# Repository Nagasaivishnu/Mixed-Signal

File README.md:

# Mixed-Signal
The following Eagle Project is just made by me to gain the experience in designing  Digital and Analog circuits.
It is 4 Layer board and JLCPCB Layer stack up has been used

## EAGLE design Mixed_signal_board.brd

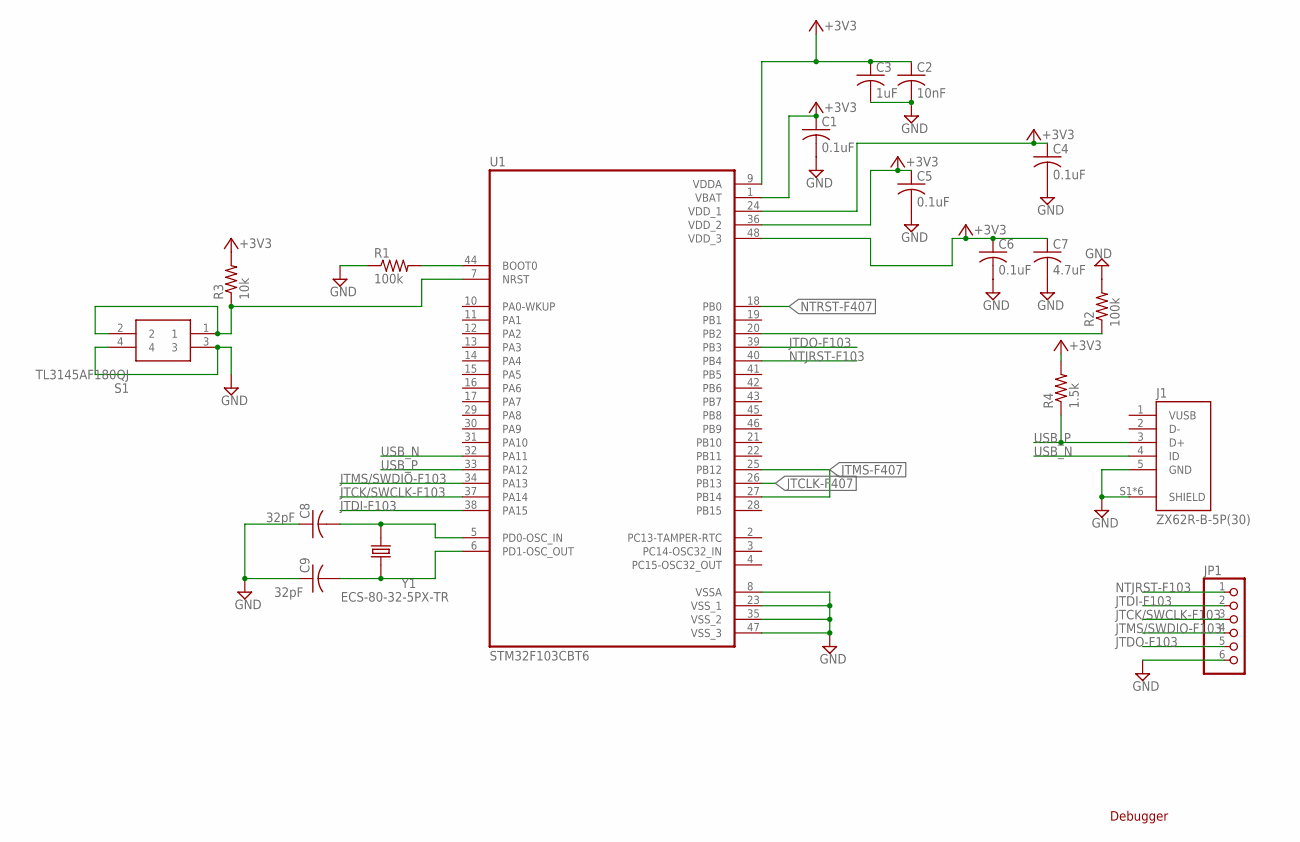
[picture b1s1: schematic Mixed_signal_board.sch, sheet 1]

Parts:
C1, C4, C5, C6: 0.1uF; C0805
C2: 10nF; C0805
C3: 1uF; C0805
C7: 4.7uF; C0805
C8, C9: 32pF; C0805
J1: ZX62R-B-5P(30); HRS_ZX62R-B-5P(30)
JP1: PINHD-1X6; 1X06
R1, R2: 100k; R0805
R3: 10k; R0805
R4: 1.5k; R0805
S1: TL3145AF180QJ
U1: STM32F103CBT6; QFP50P900X900X160-48N
Y1: ECS-80-32-5PX-TR; XTAL_ECS-80-32-5PX-TR

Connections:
+3V3: C1.1, C2.1, C3.1, C4.1, C5.1, C6.1, C7.1, R3.2, R4.2, U1.1 (VBAT), U1.9 (VDDA), U1.24 (VDD_1), U1.36 (VDD_2), U1.48 (VDD_3); also elsewhere on the board
GND: C1.2, C2.2, C3.2, C4.2, C5.2, C6.2, C7.2, C8.1, C9.1, J1.5 (GND), J1.S1 (SHIELD), J1.S2 (SHIELD), J1.S3 (SHIELD), J1.S4 (SHIELD), J1.S5 (SHIELD), J1.S6 (SHIELD), JP1.6, R1.1, R2.2, S1.3, S1.4, U1.8 (VSSA), U1.23 (VSS_1), U1.35 (VSS_2), U1.47 (VSS_3); also elsewhere on the board
JTCK/SWCLK-F103: JP1.3, U1.37 (PA14)
JTCLK-F407: U1.26 (PB13); also elsewhere on the board
JTDI-F103: JP1.2, U1.38 (PA15)
JTDO-F103: JP1.5, U1.39 (PB3)
JTMS-F407: U1.25 (PB12), U1.27 (PB14); also elsewhere on the board
JTMS/SWDIO-F103: JP1.4, U1.34 (PA13)
unnamed: R1.2, U1.44 (BOOT0)
unnamed: R2.1, U1.20 (PB2)
unnamed: C8.2, U1.5 (PD0-OSC_IN), Y1.2
unnamed: C9.2, U1.6 (PD1-OSC_OUT), Y1.1
unnamed: R3.1, S1.1, S1.2, U1.7 (NRST)
NTJRST-F103: JP1.1, U1.40 (PB4)
NTRST-F407: U1.18 (PB0)
USB_N: J1.4 (ID), U1.32 (PA11)
USB_P: J1.3 (D+), R4.1, U1.33 (PA12)

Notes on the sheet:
Debugger

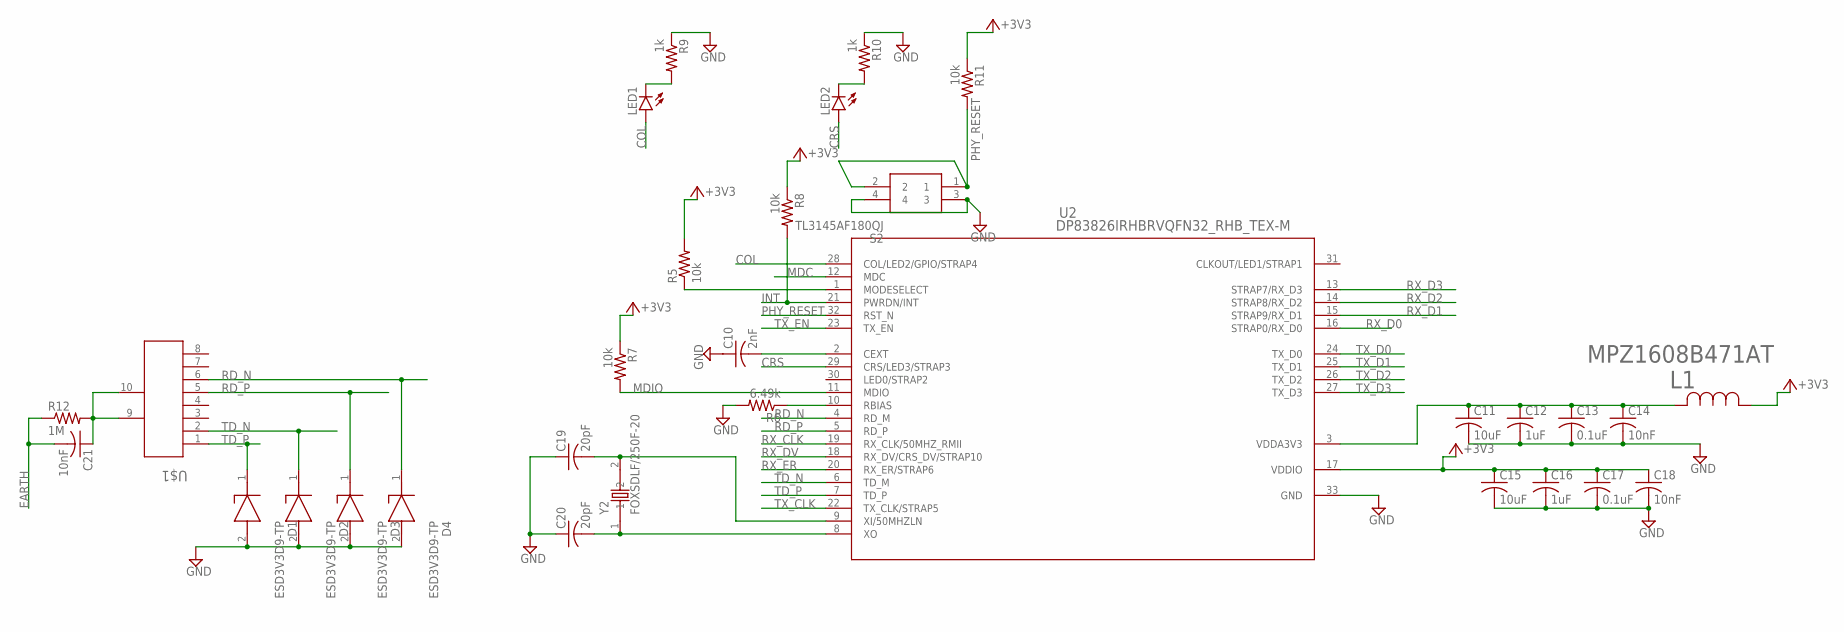
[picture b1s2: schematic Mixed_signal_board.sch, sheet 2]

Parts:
C10: 2nF; C0805
C11, C15: 10uF; C0805
C12, C16: 1uF; C0805
C13, C17: 0.1uF; C0805
C14, C18, C21: 10nF; C0805
C19, C20: 20pF; C0805
D1, D2, D3, D4: ESD3V3D9-TP; SODFL1006X43N
L1: MPZ1608B471AT; IND_MPZ1608_TDK
LED1, LED2: LEDCHIPLED_0805; CHIPLED_0805
R5, R7, R8, R11: 10k; R0805
R6: 6.49k; R0805
R9, R10: 1k; R0805
R12: 1M; R0805
S2: TL3145AF180QJ
U2: DP83826IRHBRVQFN32_RHB_TEX-M; VQFN32_RHB_TEX-M
U$1: RJ-45; CONN_RJSBE5080_16P13X12P57_AMP
Y2: FOXSDLF/250F-20; XTAL1170X500X450

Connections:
+3V3: C15.1, C16.1, C17.1, C18.1, L1.1, R5.2, R7.1, R8.1, R11.1, U2.17 (VDDIO); also elsewhere on the board
COL: LED1.A, U2.28 (COL/LED2/GPIO/STRAP4); also elsewhere on the board
CRS: LED2.A, U2.29 (CRS/LED3/STRAP3); also elsewhere on the board
EARTH: C21.2, R12.1; also elsewhere on the board
GND: C10.1, C11.2, C12.2, C13.2, C14.2, C15.2, C16.2, C17.2, C18.2, C19.1, C20.1, D1.2 (A), D2.2 (A), D3.2 (A), D4.2 (A), R6.2, R9.1, R10.1, S2.3, S2.4, U2.33 (GND); also elsewhere on the board
INT: R8.2, U2.21 (PWRDN/INT)
MDC: U2.12 (MDC); also elsewhere on the board
MDIO: R7.2, U2.11 (MDIO); also elsewhere on the board
unnamed: R5.1, U2.1 (MODESELECT)
unnamed: C10.2, U2.2 (CEXT)
unnamed: C11.1, C12.1, C13.1, C14.1, L1.2, U2.3 (VDDA3V3)
unnamed: C19.2, U2.9 (XI/50MHZLN), Y2.2
unnamed: C20.2, U2.8 (XO), Y2.1
unnamed: R6.1, U2.10 (RBIAS)
unnamed: C21.1, R12.2, U$1.9 (EARTH), U$1.10 (EARTH2)
unnamed: LED1.C, R9.2
unnamed: LED2.C, R10.2
PHY_RESET: R11.2, S2.1, S2.2, U2.32 (RST_N); also elsewhere on the board
RD_N: D4.1 (K), U2.4 (RD_M), U$1.6 (D3-)
RD_P: D3.1 (K), U2.5 (RD_P), U$1.5 (D3+)
RX_CLK: U2.19 (RX_CLK/50MHZ_RMII); also elsewhere on the board
RX_D0: U2.16 (STRAP0/RX_D0); also elsewhere on the board
RX_D1: U2.15 (STRAP9/RX_D1); also elsewhere on the board
RX_D2: U2.14 (STRAP8/RX_D2); also elsewhere on the board
RX_D3: U2.13 (STRAP7/RX_D3); also elsewhere on the board
RX_DV: U2.18 (RX_DV/CRS_DV/STRAP10); also elsewhere on the board
RX_ER: U2.20 (RX_ER/STRAP6)
TD_N: D2.1 (K), U2.6 (TD_M), U$1.2 (D1-)
TD_P: D1.1 (K), U2.7 (TD_P), U$1.1 (D1+)
TX_CLK: U2.22 (TX_CLK/STRAP5); also elsewhere on the board
TX_D0: U2.24 (TX_D0); also elsewhere on the board
TX_D1: U2.25 (TX_D1); also elsewhere on the board
TX_D2: U2.26 (TX_D2); also elsewhere on the board
TX_D3: U2.27 (TX_D3); also elsewhere on the board
TX_EN: U2.23 (TX_EN); also elsewhere on the board

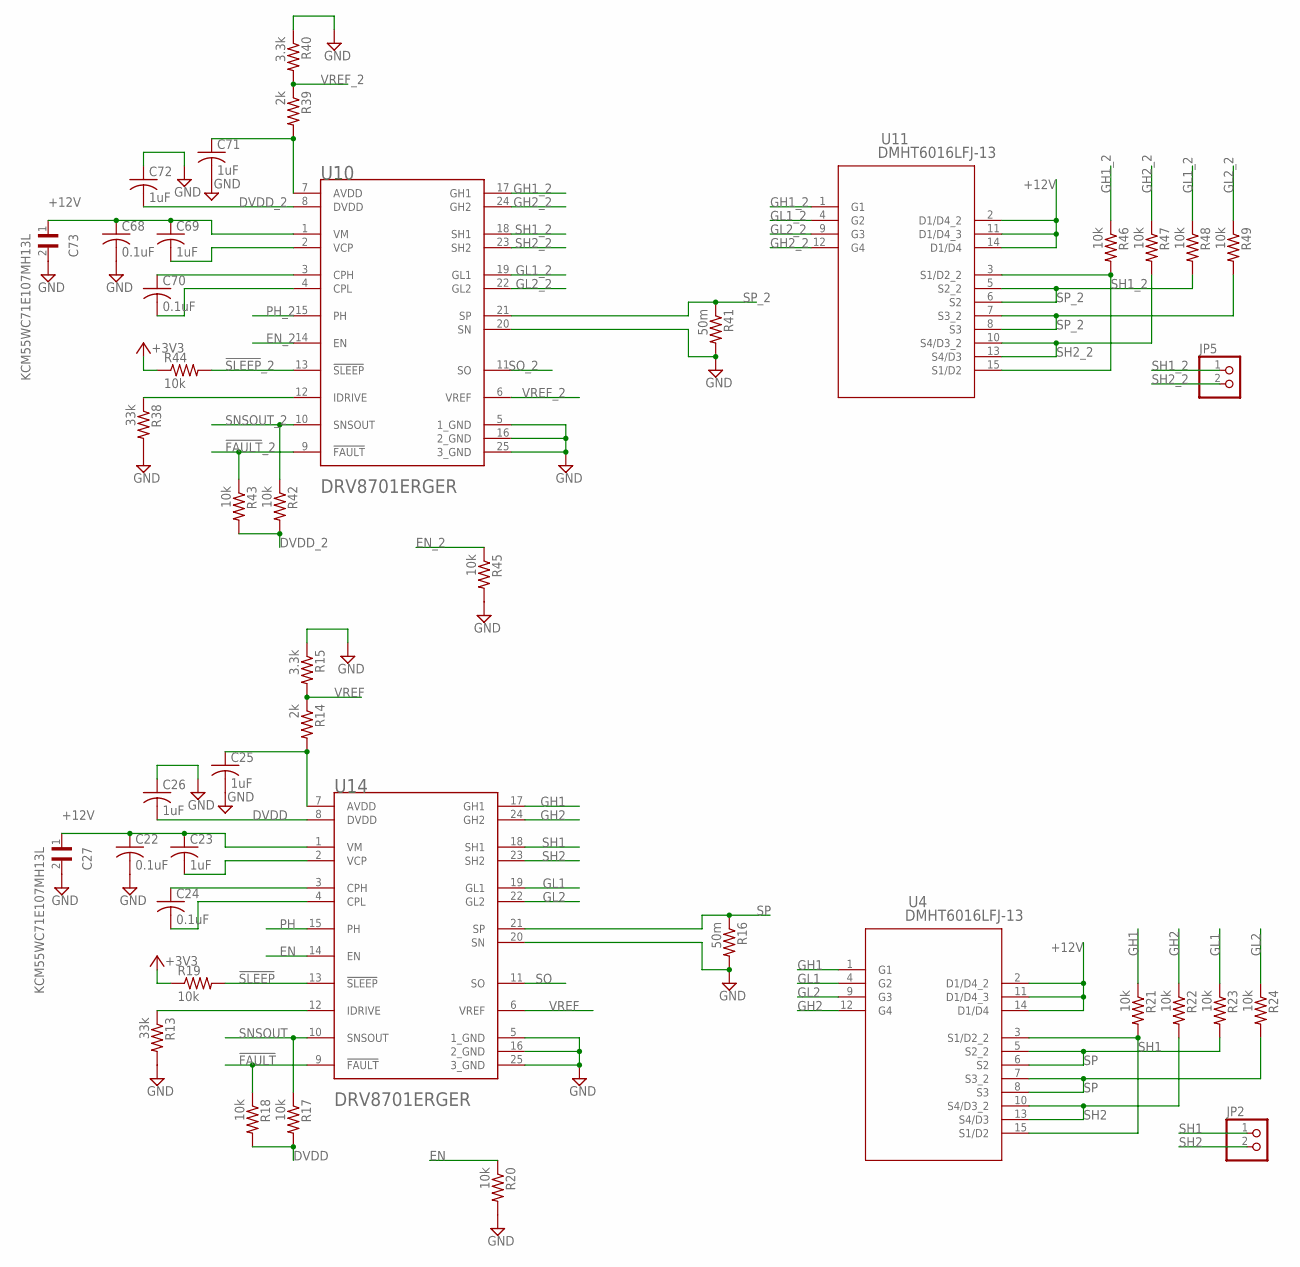
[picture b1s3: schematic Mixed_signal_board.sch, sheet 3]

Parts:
C22, C24, C68, C70: 0.1uF; C0805
C23, C25, C26, C69, C71, C72: 1uF; C0805
C27, C73: KCM55WC71E107MH13L; CAPC6153X670N
JP2, JP5: PINHD-1X2; 1X02
R13, R38: 33k; R0805
R14, R39: 2k; R0805
R15, R40: 3.3k; R0805
R16, R41: 50m; R0805
R17, R18, R19, R20, R21, R22, R23, R24, R42, R43, R44, R45, R46, R47, R48, R49: 10k; R0805
U4, U11: DMHT6016LFJ-13; QFN_LFJ-13_DIO
U10, U14: TEXAS_INSTRUMENTS_DRV8701ERGERTEXAS_INSTRUMENTS_D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; TEXAS_INSTRUMENTS_DRV8701ERGER_0

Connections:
!FAULT!: R18.1, U14.9 (!FAULT!); also elsewhere on the board
!FAULT!_2: R43.1, U10.9 (!FAULT!); also elsewhere on the board
!SLEEP!: R19.2, U14.13 (!SLEEP!)
!SLEEP!_2: R44.2, U10.13 (!SLEEP!)
+3V3: R19.1, R44.1; also elsewhere on the board
+12V: C22.1, C23.1, C27.1, C68.1, C69.1, C73.1, U4.2 (D1/D4_2), U4.11 (D1/D4_3), U4.14 (D1/D4), U10.1 (VM), U11.2 (D1/D4_2), U11.11 (D1/D4_3), U11.14 (D1/D4), U14.1 (VM); also elsewhere on the board
DVDD: C26.2, R17.2, R18.2, U14.8 (DVDD)
DVDD_2: C72.2, R42.2, R43.2, U10.8 (DVDD)
EN: R20.1, U14.14 (EN); also elsewhere on the board
EN_2: R45.1, U10.14 (EN); also elsewhere on the board
GH1: R21.1, U4.1 (G1), U14.17 (GH1)
GH1_2: R46.1, U10.17 (GH1), U11.1 (G1)
GH2: R22.1, U4.12 (G4), U14.24 (GH2)
GH2_2: R47.1, U10.24 (GH2), U11.12 (G4)
GL1: R23.1, U4.4 (G2), U14.19 (GL1)
GL1_2: R48.1, U10.19 (GL1), U11.4 (G2)
GL2: R24.1, U4.9 (G3), U14.22 (GL2)
GL2_2: R49.1, U10.22 (GL2), U11.9 (G3)
GND: C22.2, C25.2, C26.1, C27.2, C68.2, C71.2, C72.1, C73.2, R13.2, R15.1, R16.2, R20.2, R38.2, R40.1, R41.2, R45.2, U10.5 (1_GND), U10.16 (2_GND), U10.20 (SN), U10.25 (3_GND), U14.5 (1_GND), U14.16 (2_GND), U14.20 (SN), U14.25 (3_GND); also elsewhere on the board
unnamed: C23.2, U14.2 (VCP)
unnamed: C24.1, U14.3 (CPH)
unnamed: C24.2, U14.4 (CPL)
unnamed: R13.1, U14.12 (IDRIVE)
unnamed: C25.1, R14.2, U14.7 (AVDD)
unnamed: C69.2, U10.2 (VCP)
unnamed: C70.1, U10.3 (CPH)
unnamed: C70.2, U10.4 (CPL)
unnamed: R38.1, U10.12 (IDRIVE)
unnamed: C71.1, R39.2, U10.7 (AVDD)
PH: U14.15 (PH); also elsewhere on the board
PH_2: U10.15 (PH); also elsewhere on the board
SH1: JP2.1, R21.2, U4.3 (S1/D2_2), U4.15 (S1/D2), U14.18 (SH1)
SH1_2: JP5.1, R46.2, U10.18 (SH1), U11.3 (S1/D2_2), U11.15 (S1/D2)
SH2: JP2.2, R22.2, U4.10 (S4/D3_2), U4.13 (S4/D3), U14.23 (SH2)
SH2_2: JP5.2, R47.2, U10.23 (SH2), U11.10 (S4/D3_2), U11.13 (S4/D3)
SNSOUT: R17.1, U14.10 (SNSOUT); also elsewhere on the board
SNSOUT_2: R42.1, U10.10 (SNSOUT); also elsewhere on the board
SO: U14.11 (SO); also elsewhere on the board
SO_2: U10.11 (SO); also elsewhere on the board
SP: R16.1, R23.2, R24.2, U4.5 (S2_2), U4.6 (S2), U4.7 (S3_2), U4.8 (S3), U14.21 (SP)
SP_2: R41.1, R48.2, R49.2, U10.21 (SP), U11.5 (S2_2), U11.6 (S2), U11.7 (S3_2), U11.8 (S3)
VREF: R14.1, R15.2, U14.6 (VREF)
VREF_2: R39.1, R40.2, U10.6 (VREF)

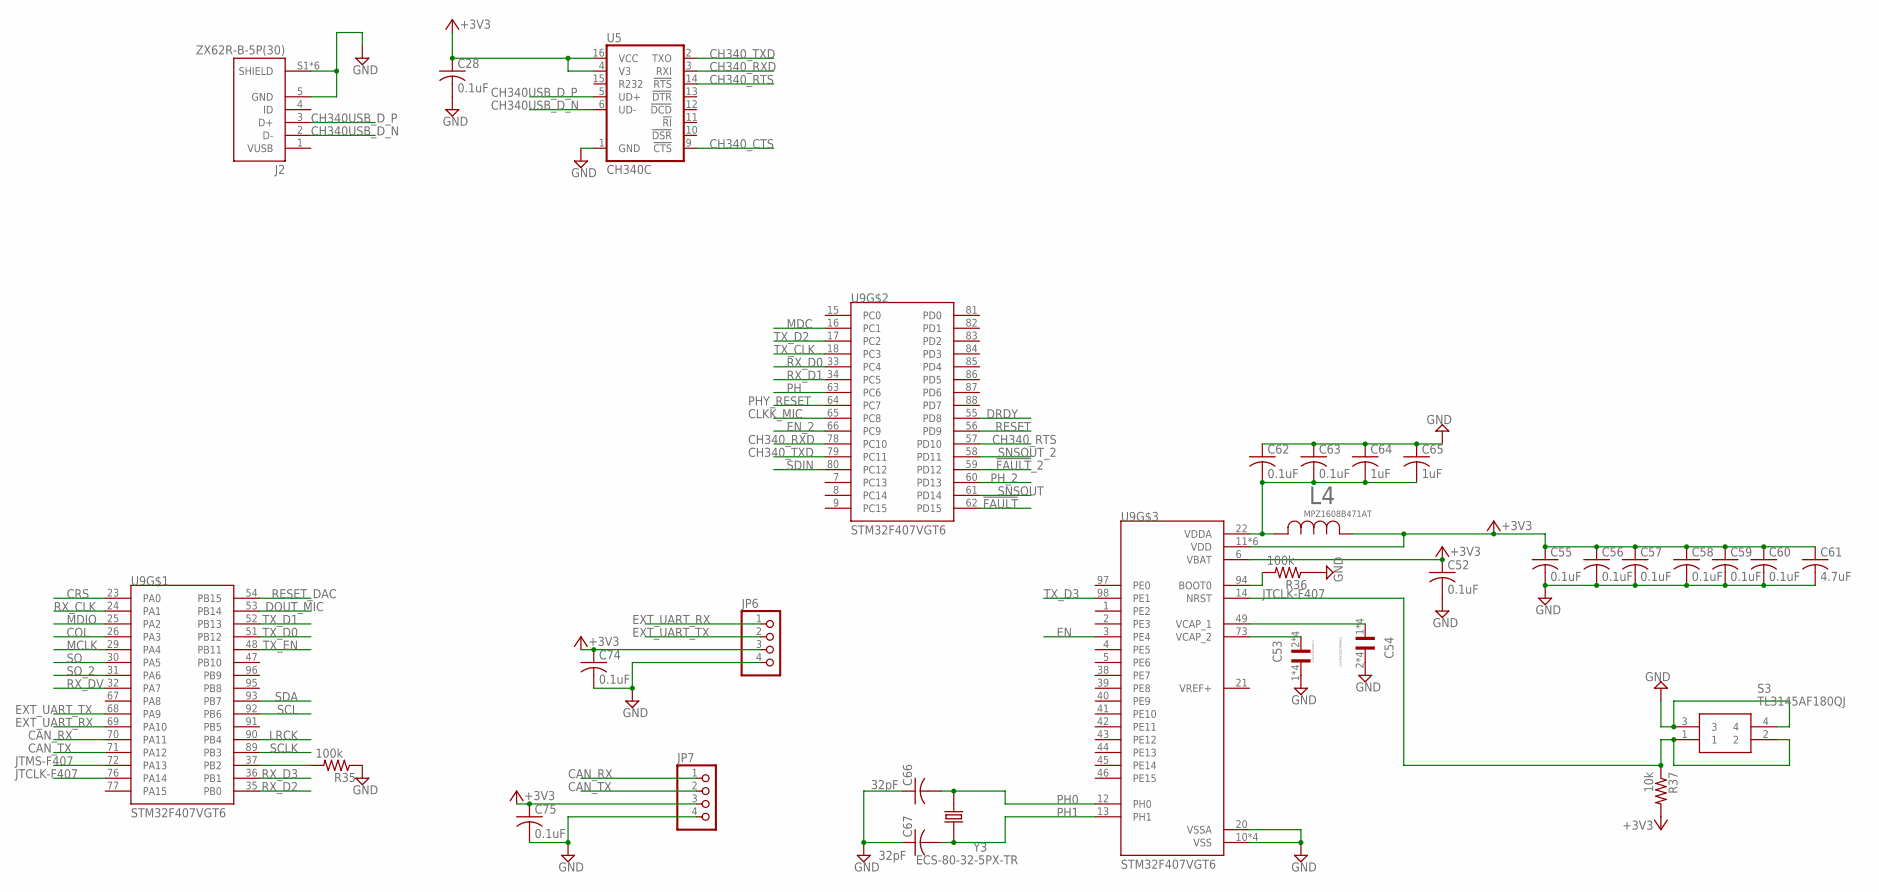
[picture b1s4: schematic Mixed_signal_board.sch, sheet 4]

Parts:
C28, C52, C55, C56, C57, C58, C59, C60, C62, C63, C74, C75: 0.1uF; C0805
C53, C54: LLA219C70G225MA01L; CAP_LLA219C70G225MA01L
C61: 4.7uF; C0805
C64, C65: 1uF; C0805
C66, C67: 32pF; C0805
J2: ZX62R-B-5P(30); HRS_ZX62R-B-5P(30)
JP6, JP7: PINHD-1X4; 1X04
L4: MPZ1608B471AT; IND_MPZ1608_TDK
R35, R36: 100k; R0805
R37: 10k; R0805
S3: TL3145AF180QJ
U5: CH340C; SO016
U9: STM32F407VGT6; QFP50P1600X1600X160-100N
Y3: ECS-80-32-5PX-TR; XTAL_ECS-80-32-5PX-TR

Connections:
!FAULT!: U9.62 (PD15); also elsewhere on the board
!FAULT!_2: U9.59 (PD12); also elsewhere on the board
+3V3: C28.1, C52.1, C55.1, C56.1, C57.1, C58.1, C59.1, C60.1, C61.1, C74.1, C75.1, JP6.3, JP7.3, L4.1, R37.2, U5.4 (V3), U5.16 (VCC), U9.6 (VBAT), U9.11 (VDD), U9.19 (VDD), U9.28 (VDD), U9.50 (VDD), U9.75 (VDD), U9.100 (VDD); also elsewhere on the board
CAN_RX: JP7.1, U9.70 (PA11)
CAN_TX: JP7.2, U9.71 (PA12)
CH340USB_D_N: J2.2 (D-), U5.6 (UD-)
CH340USB_D_P: J2.3 (D+), U5.5 (UD+)
CH340_CTS: U5.9 (!CTS)
CH340_RTS: U5.14 (!RTS), U9.57 (PD10)
CH340_RXD: U5.3 (RXI), U9.78 (PC10)
CH340_TXD: U5.2 (TXO), U9.79 (PC11)
CLKK_MIC: U9.65 (PC8); also elsewhere on the board
COL: U9.26 (PA3); also elsewhere on the board
CRS: U9.23 (PA0); also elsewhere on the board
DOUT_MIC: U9.53 (PB14); also elsewhere on the board
DRDY: U9.55 (PD8); also elsewhere on the board
EN: U9.3 (PE4); also elsewhere on the board
EN_2: U9.66 (PC9); also elsewhere on the board
EXT_UART_RX: JP6.1, U9.69 (PA10)
EXT_UART_TX: JP6.2, U9.68 (PA9)
GND: C28.2, C52.2, C53.1, C53.3 (1), C53.5 (1), C53.7 (1), C54.2, C54.4 (2), C54.6 (2), C54.8 (2), C55.2, C56.2, C57.2, C58.2, C59.2, C60.2, C61.2, C62.1, C63.1, C64.1, C65.1, C66.1, C67.1, C74.2, C75.2, J2.5 (GND), J2.S1 (SHIELD), J2.S2 (SHIELD), J2.S3 (SHIELD), J2.S4 (SHIELD), J2.S5 (SHIELD), J2.S6 (SHIELD), JP6.4, JP7.4, R35.1, R36.1, S3.3, S3.4, U5.1 (GND), U9.10 (VSS), U9.20 (VSSA), U9.27 (VSS), U9.74 (VSS), U9.99 (VSS); also elsewhere on the board
JTCLK-F407: R37.1, S3.1, S3.2, U9.14 (NRST), U9.76 (PA14); also elsewhere on the board
JTMS-F407: U9.72 (PA13); also elsewhere on the board
LRCK: U9.90 (PB4); also elsewhere on the board
MCLK: U9.29 (PA4); also elsewhere on the board
MDC: U9.16 (PC1); also elsewhere on the board
MDIO: U9.25 (PA2); also elsewhere on the board
unnamed: R36.2, U9.94 (BOOT0)
unnamed: C54.1, C54.3 (1), C54.5 (1), C54.7 (1), U9.49 (VCAP_1)
unnamed: C53.2, C53.4 (2), C53.6 (2), C53.8 (2), U9.73 (VCAP_2)
unnamed: C62.2, C63.2, C64.2, C65.2, L4.2, U9.22 (VDDA)
unnamed: R35.2, U9.37 (PB2)
PH: U9.63 (PC6); also elsewhere on the board
PH0: C66.2, U9.12 (PH0), Y3.2
PH1: C67.2, U9.13 (PH1), Y3.1
PHY_RESET: U9.64 (PC7); also elsewhere on the board
PH_2: U9.60 (PD13); also elsewhere on the board
RESET: U9.56 (PD9); also elsewhere on the board
RESET_DAC: U9.54 (PB15); also elsewhere on the board
RX_CLK: U9.24 (PA1); also elsewhere on the board
RX_D0: U9.33 (PC4); also elsewhere on the board
RX_D1: U9.34 (PC5); also elsewhere on the board
RX_D2: U9.35 (PB0); also elsewhere on the board
RX_D3: U9.36 (PB1); also elsewhere on the board
RX_DV: U9.32 (PA7); also elsewhere on the board
SCL: U9.92 (PB6); also elsewhere on the board
SCLK: U9.89 (PB3); also elsewhere on the board
SDA: U9.93 (PB7); also elsewhere on the board
SDIN: U9.80 (PC12); also elsewhere on the board
SNSOUT: U9.61 (PD14); also elsewhere on the board
SNSOUT_2: U9.58 (PD11); also elsewhere on the board
SO: U9.30 (PA5); also elsewhere on the board
SO_2: U9.31 (PA6); also elsewhere on the board
TX_CLK: U9.18 (PC3); also elsewhere on the board
TX_D0: U9.51 (PB12); also elsewhere on the board
TX_D1: U9.52 (PB13); also elsewhere on the board
TX_D2: U9.17 (PC2); also elsewhere on the board
TX_D3: U9.98 (PE1); also elsewhere on the board
TX_EN: U9.48 (PB11); also elsewhere on the board
VREF+: U9.21 (VREF+)

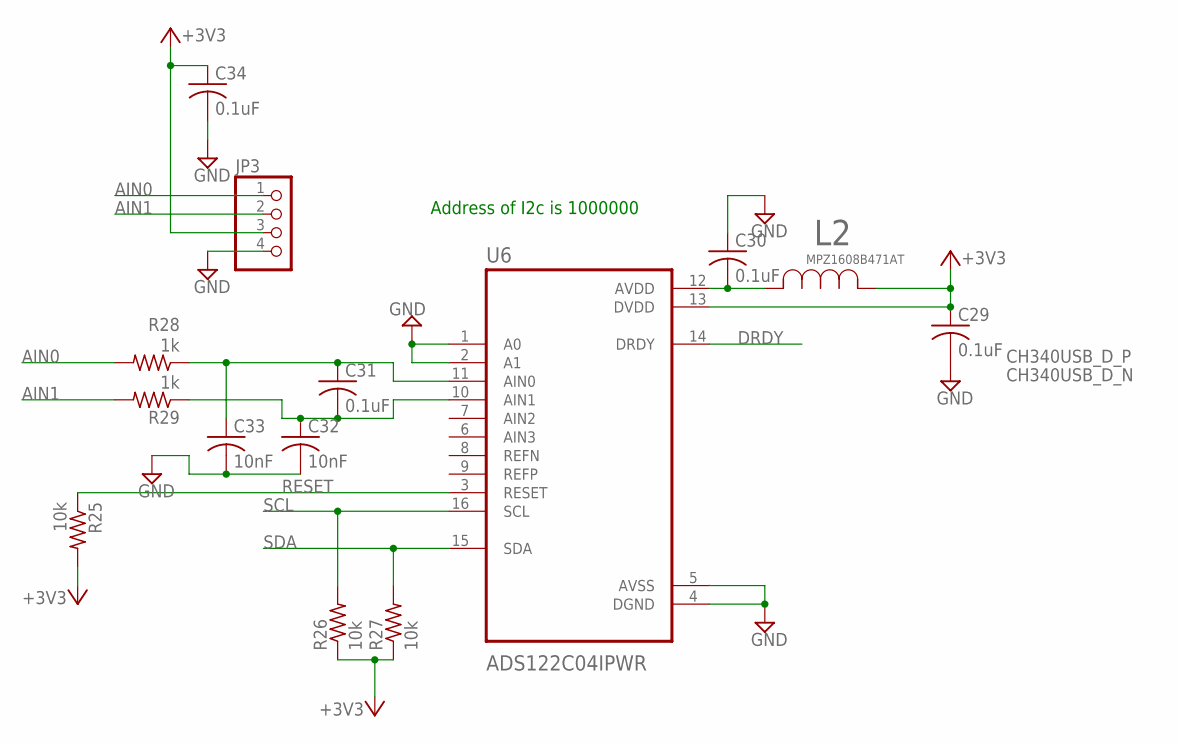
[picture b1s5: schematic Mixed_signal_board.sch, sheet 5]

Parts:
C29, C30, C31, C34: 0.1uF; C0805
C32, C33: 10nF; C0805
JP3: PINHD-1X4; 1X04
L2: MPZ1608B471AT; IND_MPZ1608_TDK
R25, R26, R27: 10k; R0805
R28, R29: 1k; R0805
U6: ADS122C04IPWR; SOP65P640X120-16N

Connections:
+3V3: C29.1, C34.1, JP3.3, L2.1, R25.2, R26.1, R27.1, U6.13 (DVDD); also elsewhere on the board
AIN0: JP3.1, R28.2
AIN1: JP3.2, R29.2
DRDY: U6.14 (DRDY); also elsewhere on the board
GND: C29.2, C30.1, C32.2, C33.2, C34.2, JP3.4, U6.1 (A0), U6.2 (A1), U6.4 (DGND), U6.5 (AVSS); also elsewhere on the board
unnamed: C30.2, L2.2, U6.12 (AVDD)
unnamed: C31.1, C33.1, R28.1, U6.11 (AIN0)
unnamed: C31.2, C32.1, R29.1, U6.10 (AIN1)
RESET: R25.1, U6.3 (RESET); also elsewhere on the board
SCL: R26.2, U6.16 (SCL); also elsewhere on the board
SDA: R27.2, U6.15 (SDA); also elsewhere on the board

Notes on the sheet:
Address of I2c is 1000000

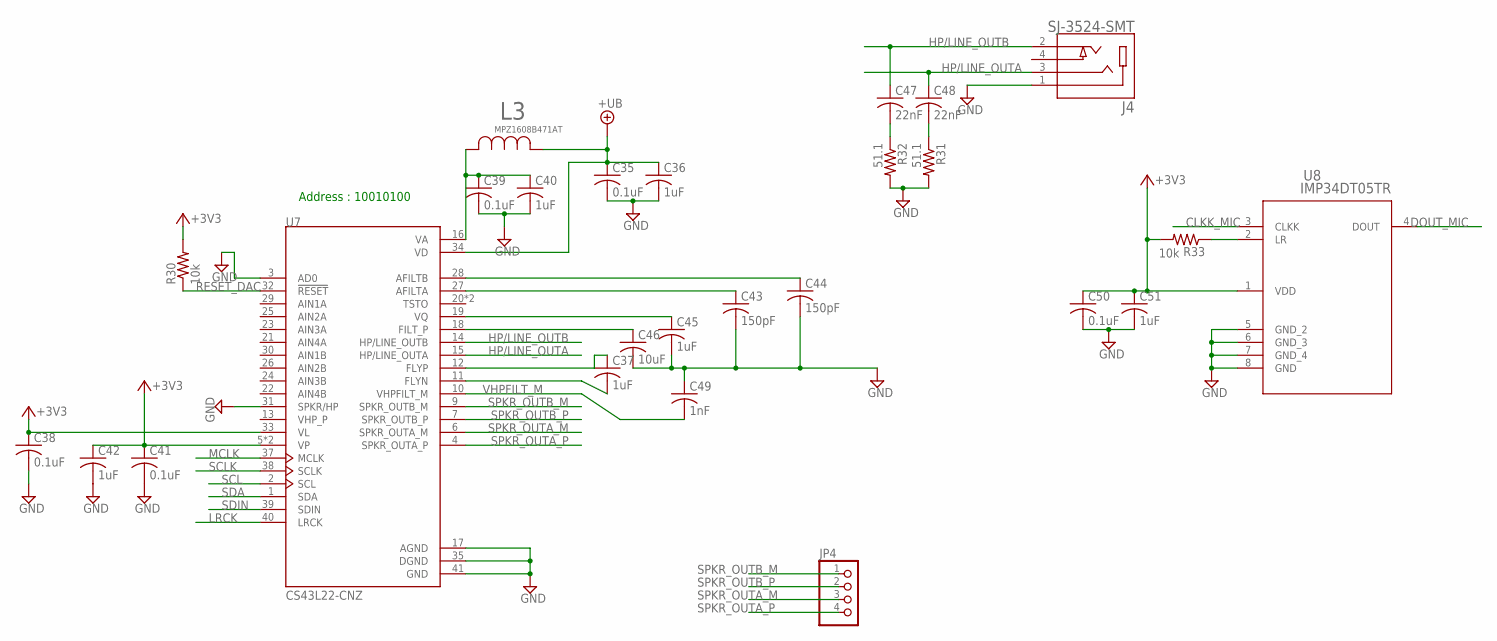
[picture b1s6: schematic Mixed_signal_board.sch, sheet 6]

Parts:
C35, C38, C39, C41, C50: 0.1uF; C0805
C36, C37, C40, C42, C45, C51: 1uF; C0805
C43, C44: 150pF; C0805
C46: 10uF; C0805
C47, C48: 22nF; C0805
C49: 1nF; C0805
J4: SJ-3524-SMT; CUI_SJ-3524-SMT
JP4: PINHD-1X4; 1X04
L3: MPZ1608B471AT; IND_MPZ1608_TDK
R30, R33: 10k; R0805
R31, R32: 51.1; R0805
U7: CS43L22-CNZ; QFN50P600X600X100-41N
U8: IMP34DT05TR; HCLGA_3X4X1_STM

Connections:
+3V3: C38.1, C41.1, C42.1, C50.1, C51.1, R30.2, R33.2, U7.5 (VP), U7.8 (VP), U7.33 (VL), U8.1 (VDD); also elsewhere on the board
+UB: C35.1, C36.1, L3.1, U7.34 (VD); also elsewhere on the board
CLKK_MIC: U8.3 (CLKK); also elsewhere on the board
DOUT_MIC: U8.4 (DOUT); also elsewhere on the board
GND: C35.2, C36.2, C38.2, C39.2, C40.2, C41.2, C42.2, C43.2, C44.2, C45.2, C46.2, C49.1, C50.2, C51.2, J4.1, R31.2, R32.2, U7.3 (AD0), U7.17 (AGND), U7.31 (SPKR/HP), U7.35 (DGND), U7.41 (GND), U8.5 (GND_2), U8.6 (GND_3), U8.7 (GND_4), U8.8 (GND); also elsewhere on the board
HP/LINE_OUTA: C48.1, J4.3, U7.15 (HP/LINE_OUTA)
HP/LINE_OUTB: C47.1, J4.2, U7.14 (HP/LINE_OUTB)
LRCK: U7.40 (LRCK); also elsewhere on the board
MCLK: U7.37 (MCLK); also elsewhere on the board
unnamed: C37.1, U7.12 (FLYP)
unnamed: C37.2, U7.11 (FLYN)
unnamed: C39.1, C40.1, L3.2, U7.16 (VA)
unnamed: C43.1, U7.27 (AFILTA)
unnamed: C44.1, U7.28 (AFILTB)
unnamed: C45.1, U7.19 (VQ)
unnamed: C47.2, R32.1
unnamed: C46.1, U7.18 (FILT_P)
unnamed: C48.2, R31.1
unnamed: R33.1, U8.2 (LR)
RESET_DAC: R30.1, U7.32 (!RESET); also elsewhere on the board
SCL: U7.2 (SCL); also elsewhere on the board
SCLK: U7.38 (SCLK); also elsewhere on the board
SDA: U7.1 (SDA); also elsewhere on the board
SDIN: U7.39 (SDIN); also elsewhere on the board
SPKR_OUTA_M: JP4.3, U7.6 (SPKR_OUTA_M)
SPKR_OUTA_P: JP4.4, U7.4 (SPKR_OUTA_P)
SPKR_OUTB_M: JP4.1, U7.9 (SPKR_OUTB_M)
SPKR_OUTB_P: JP4.2, U7.7 (SPKR_OUTB_P)
VHPFILT_M: C49.2, U7.10 (VHPFILT_M)

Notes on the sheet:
Address : 10010100

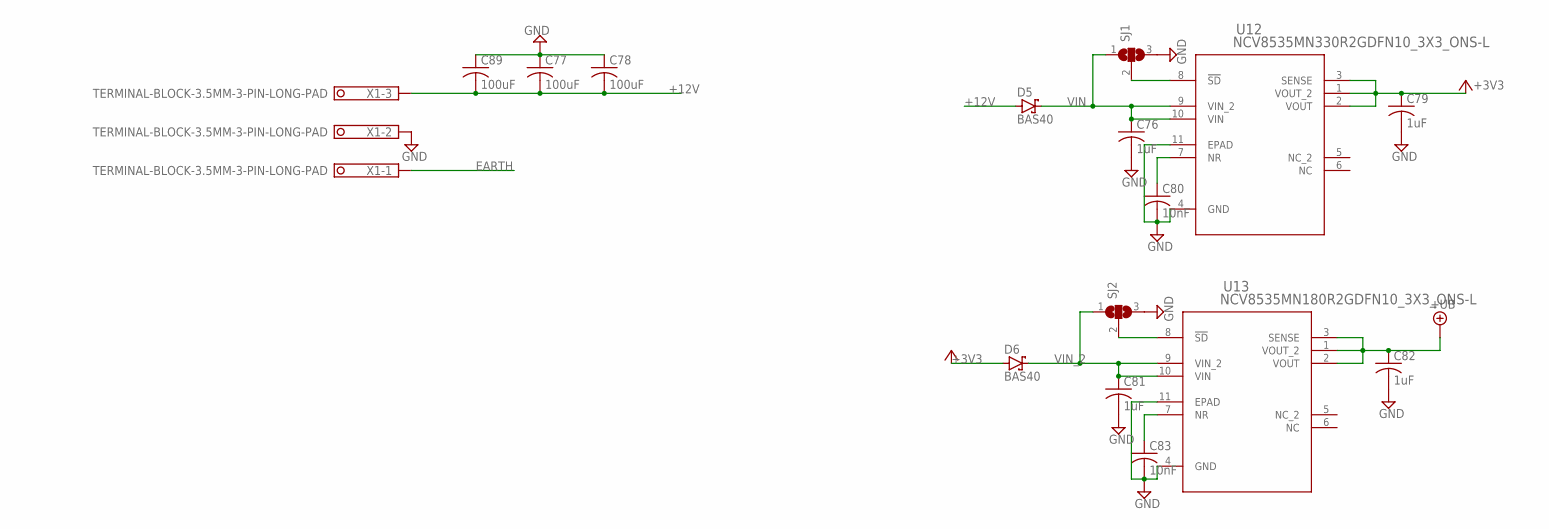
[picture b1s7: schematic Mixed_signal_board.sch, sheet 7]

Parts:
C76, C79, C81, C82: 1uF; C0805
C77, C78, C89: 100uF; C0805
C80, C83: 10nF; C0805
D5, D6: BAS40; SOT23
SJ1, SJ2: SJ2WW; SJ_2W
U12: NCV8535MN330R2GDFN10_3X3_ONS-L; DFN10_3X3_ONS-L
U13: NCV8535MN180R2GDFN10_3X3_ONS-L; DFN10_3X3_ONS-L
X1: TERMINAL-BLOCK-3.5MM-3-PIN-LONG-PAD; TERMINAL-BLOCK-3-PIN-3.5MM-LONG-PAD

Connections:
+3V3: C79.1, D6.1 (A), U12.1 (VOUT_2), U12.2 (VOUT), U12.3 (SENSE); also elsewhere on the board
+12V: C77.2, C78.2, C89.2, D5.1 (A), X1.3; also elsewhere on the board
+UB: C82.1, U13.1 (VOUT_2), U13.2 (VOUT), U13.3 (SENSE); also elsewhere on the board
EARTH: X1.1; also elsewhere on the board
GND: C76.2, C77.1, C78.1, C79.2, C80.2, C81.2, C82.2, C83.2, C89.1, SJ1.3, SJ2.3, U12.4 (GND), U12.11 (EPAD), U13.4 (GND), U13.11 (EPAD), X1.2; also elsewhere on the board
unnamed: SJ1.2, U12.8 (!SD)
unnamed: C83.1, U13.7 (NR)
unnamed: SJ2.2, U13.8 (!SD)
unnamed: C80.1, U12.7 (NR)
VIN: C76.1, D5.3 (C), SJ1.1, U12.9 (VIN_2), U12.10 (VIN)
VIN_2: C81.1, D6.3 (C), SJ2.1, U13.9 (VIN_2), U13.10 (VIN)

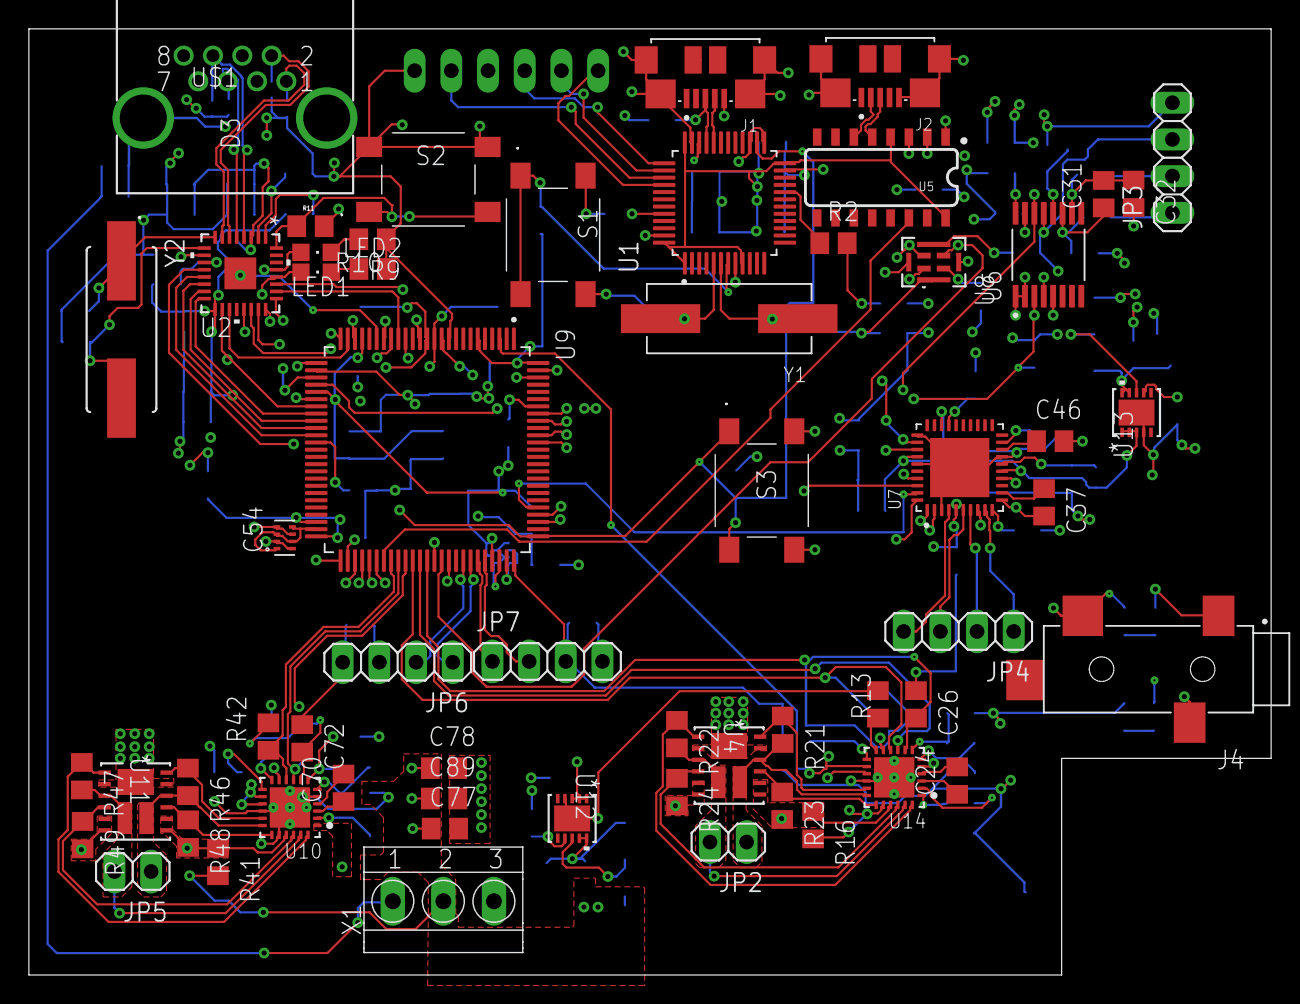
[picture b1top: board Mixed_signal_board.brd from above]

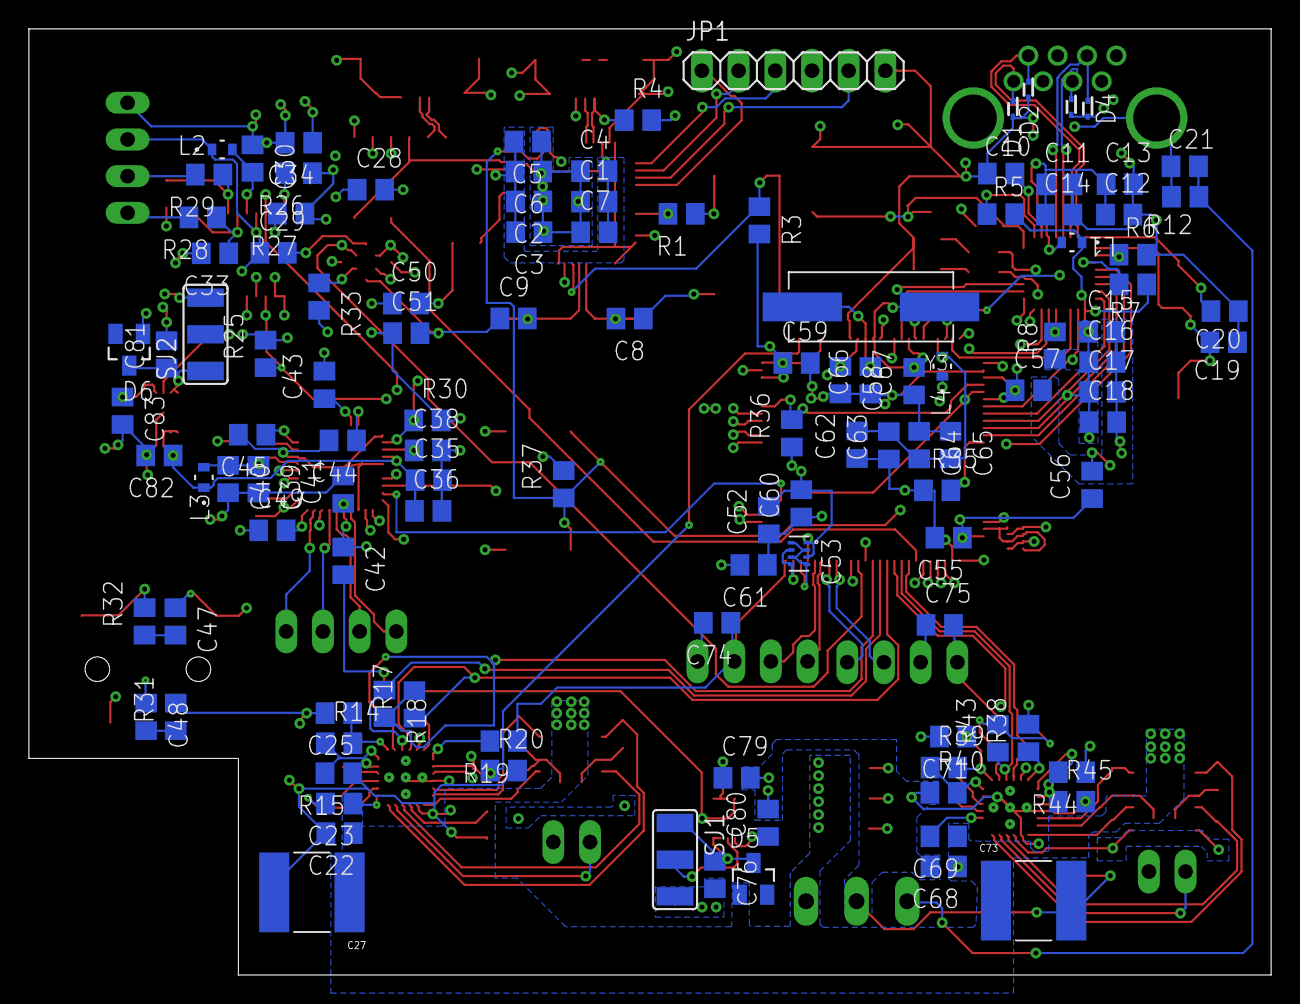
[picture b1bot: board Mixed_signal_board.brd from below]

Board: 4 copper layers, 86.0 x 65.5 mm, 177 parts (118 on the bottom side), 145 nets.

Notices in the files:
parts and their libraries:
COPYRIGHT: Copyright (C) 2018 Accelerated Designs. All rights reserved
COPYRIGHT: Copyright (C) 2016 Accelerated Designs. All rights reserved
